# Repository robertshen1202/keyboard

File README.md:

# keyboard-pcb

Hello! This is my repo for keeping keyboard design related stuff. Please check the readme inside each layout folder for more detailed information. 

Progress Tracker: 

- ✔️ - finished
- 🚧 - in progress
- ❌ - not started yet

Layout | Current Version | Progress 
--- | --- | --- 
numpad | 1.0 | 🚧
1800 | N/A | ❌
60 percent | N/A | ❌

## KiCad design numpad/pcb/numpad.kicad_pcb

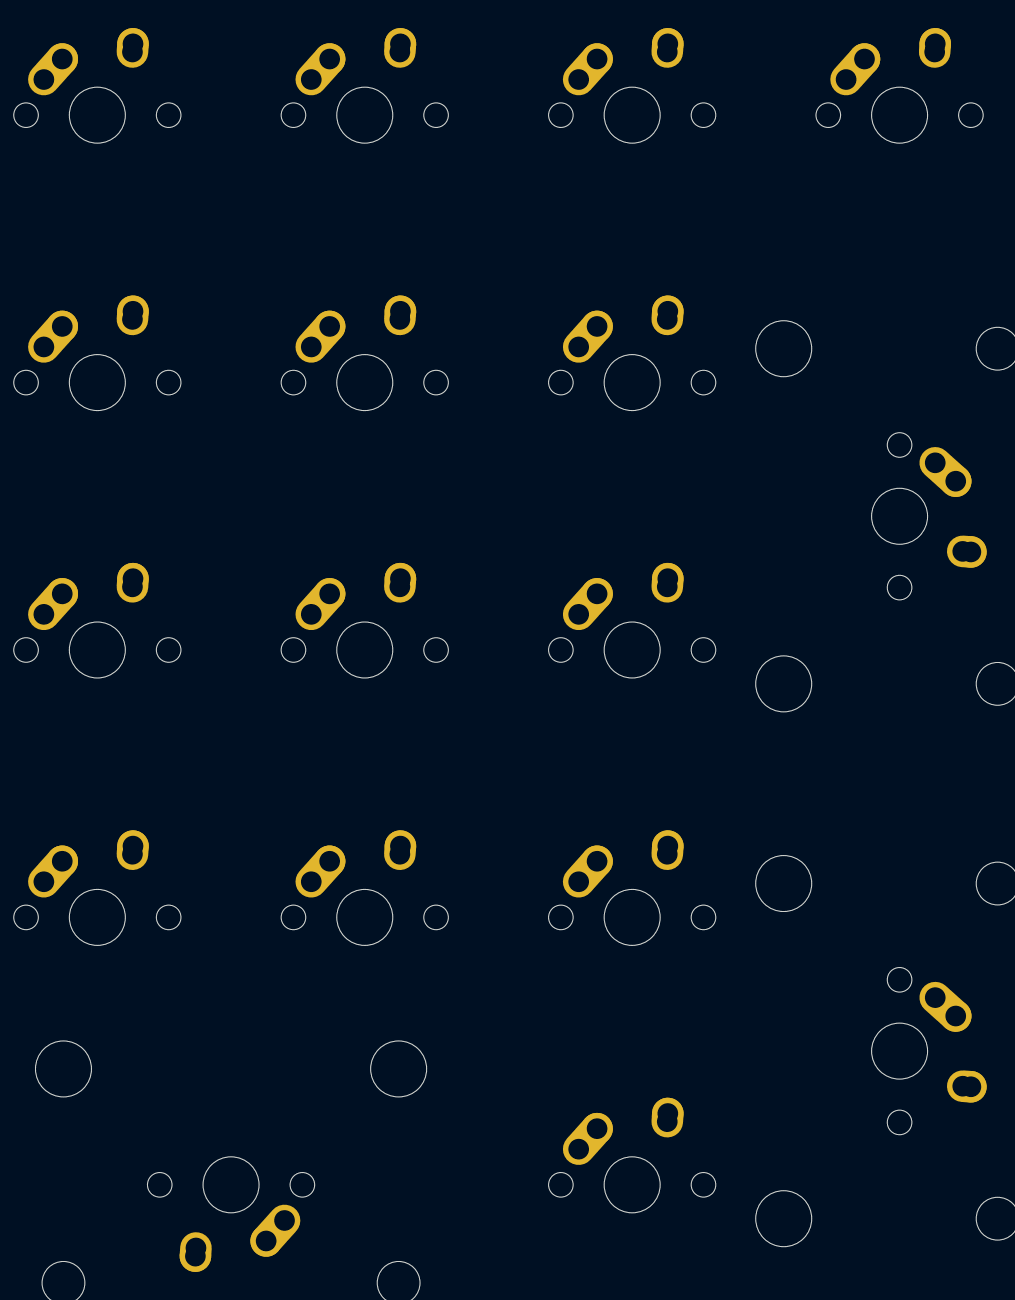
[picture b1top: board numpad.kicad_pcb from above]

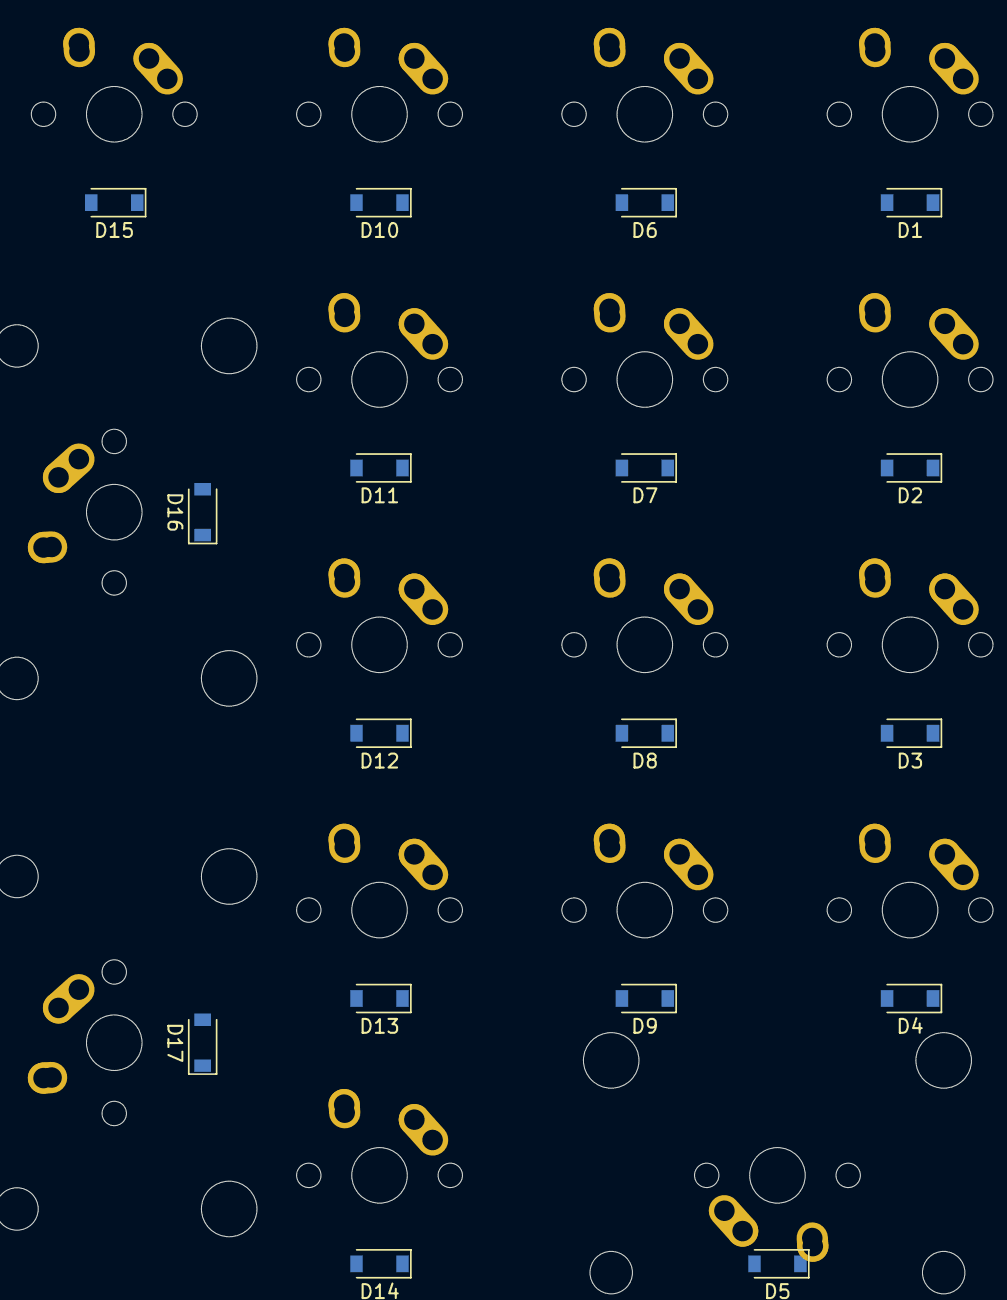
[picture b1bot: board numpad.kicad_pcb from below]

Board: 2 copper layers, 34 parts (17 on the bottom side), 26 nets, no tracks yet.

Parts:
D1, D2, D3, D4, D5, D6, D7, D8, D9, D10, D11, D12, D13, D14, D15, D16, D17: BAT42W-V; D_SOD-123
MX1, MX2, MX3, MX4, MX6, MX7, MX8, MX9, MX10, MX11, MX12, MX13, MX14, MX15: MX-NoLED; MX-1U-NoLED
MX5, MX16, MX17: MX-NoLED; MX-2U-NoLED

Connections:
unnamed: D1.1, D6.1, D10.1, D15.1
unnamed: D1.2, MX1.2
unnamed: D2.2, MX2.2
unnamed: D3.2, MX3.2
unnamed: D4.2, MX4.2
unnamed: D5.2, MX5.2
unnamed: D6.2, MX6.2
unnamed: D7.2, MX7.2
unnamed: D8.2, MX8.2
unnamed: D9.2, MX9.2
unnamed: D10.2, MX10.2
unnamed: D2.1, D7.1, D11.1, D16.1
unnamed: D11.2, MX11.2
unnamed: D3.1, D8.1, D12.1
unnamed: D12.2, MX12.2
unnamed: D4.1, D9.1, D13.1, D17.1
unnamed: D13.2, MX13.2
unnamed: D5.1, D14.1
unnamed: D14.2, MX14.2
unnamed: D15.2, MX15.2
unnamed: D16.2, MX16.2
unnamed: D17.2, MX17.2
unnamed: MX1.1, MX2.1, MX3.1, MX4.1, MX5.1
unnamed: MX6.1, MX7.1, MX8.1, MX9.1
unnamed: MX10.1, MX11.1, MX12.1, MX13.1, MX14.1
unnamed: MX15.1, MX16.1, MX17.1

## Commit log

2021-03-28 added key matrix in both schematic and layout
2021-08-31 inital upload
2021-08-31 put files in pcb, case, and layout folder
2021-09-06 serpated schematic into multisheet and reset annotation in sheet_num*1000
2021-09-06 added welcome message and progress tracker
2021-09-06 initial upload
2021-09-06 fixed progress tracker
2021-09-06 changed status emoji
2021-09-08 updated all net label and connected the sheet pins
2021-09-09 removed rescued lib to fix some footprint issue
2024-01-13 added step file for cherry mx switches and 2u stab
2024-01-21 added step files for numpad cases
2024-01-22 added dxf and svg output for the keyboard layout
